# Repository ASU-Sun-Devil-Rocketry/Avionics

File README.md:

<h1>Sun Devil Rocketry Avionics</h1>

This is a repository for all SDR Avionics software and PCB files. Current Projects include:
<ul>
   <li>General Purpose Flight Computer</li>
   <li>Ground Station Launch System</li>
   <li>Strand Burner Ignition and Data Acquisition System</li>
   <li>Liquid Propulsion Propellant Management Controller and Data Acquisition Systems</li>
</ul>
     
Files related to the flight computer and ground station can be found in the general directory. Strand Burner files can be found in the solids directory, and liquid propulsion files can be found in the liquids folder.

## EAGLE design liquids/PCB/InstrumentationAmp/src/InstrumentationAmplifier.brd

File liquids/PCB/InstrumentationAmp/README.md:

<h1>Instrumentation Amplifier with Regulated Dual Supply</h1>

The instrumentation amplifier uses an adjustable gain differential amplifier with buffered inputs to amplify the readings from an analog sensor using a wheatstone bridge such as a load cell or pressure transducer. The operational amplifiers use a dual power supply which is regulated using variable linear voltage regulators.

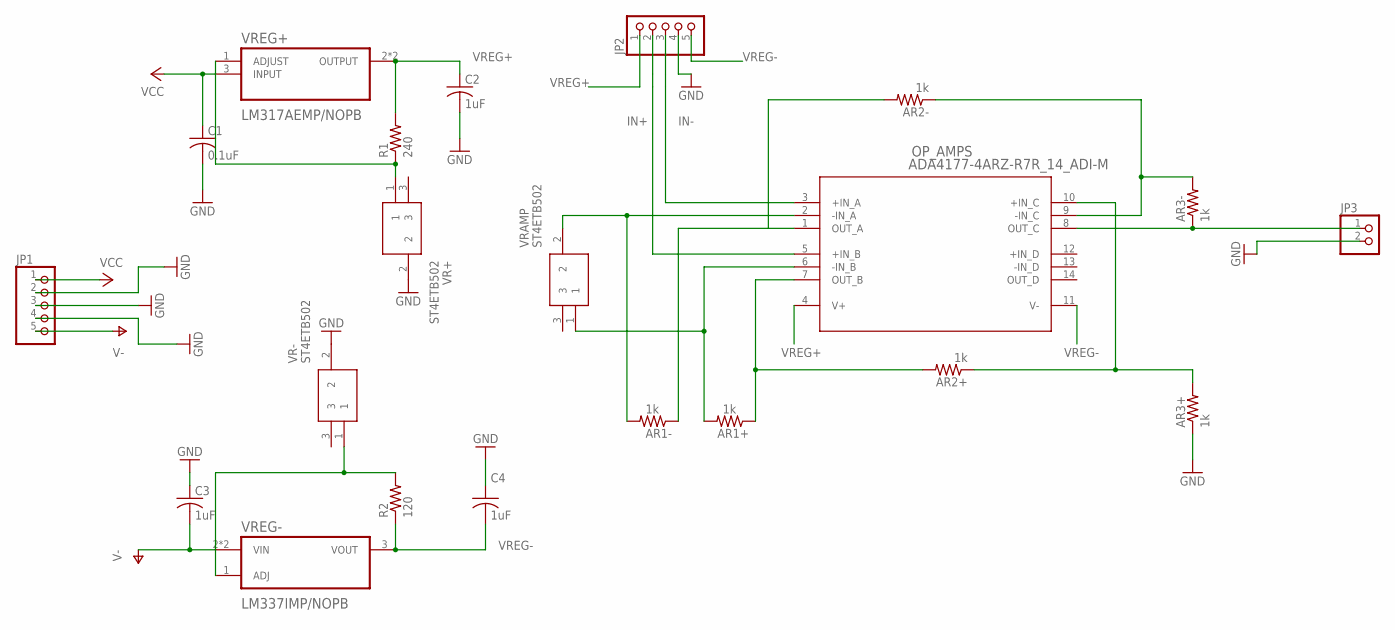
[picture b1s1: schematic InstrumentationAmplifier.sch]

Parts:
AR1+, AR1-, AR2+, AR2-, AR3+, AR3-: 1k; R0603
C1: 0.1uF; C0603
C2, C3, C4: 1uF; C0603
JP1, JP2: PINHD-1X55X2MM; 1_05X2MM
JP3: PINHD-1X2; 1X02
OP_AMPS: ADA4177-4ARZ-R7R_14_ADI-M; R_14_ADI-M
R1: 240; R0603
R2: 120; R0603
VR+: ST4ETB502; ST-4EB
VR-: ST4ETB502; ST-4EB
VRAMP: ST4ETB502; ST-4EB
VREG+: LM317AEMP/NOPB; SOT230P700X180-4N
VREG-: LM337IMP/NOPB; SOT230P700X180-4N

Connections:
GND: AR3+.1, C1.2, C2.2, C3.1, C4.1, JP1.2, JP1.3, JP1.4, JP2.4, JP3.2, VR+.2, VR-.2
IN+: JP2.2, OP_AMPS.5 (+IN_B)
IN-: JP2.3, OP_AMPS.3 (+IN_A)
unnamed: AR2+.1, AR3+.2, OP_AMPS.10 (+IN_C)
unnamed: R1.1, VR+.1, VREG+.1 (ADJUST)
unnamed: AR2-.1, AR3-.2, OP_AMPS.9 (-IN_C)
unnamed: R2.2, VR-.1, VREG-.1 (ADJ)
unnamed: AR1-.1, AR2-.2, OP_AMPS.1 (OUT_A)
unnamed: AR1-.2, OP_AMPS.2 (-IN_A), VRAMP.2
unnamed: AR1+.1, AR2+.2, OP_AMPS.7 (OUT_B)
unnamed: AR1+.2, OP_AMPS.6 (-IN_B), VRAMP.1
unnamed: AR3-.1, JP3.1, OP_AMPS.8 (OUT_C)
V-: C3.2, JP1.5, VREG-.2 (VIN), VREG-.4 (VIN)
VCC: C1.1, JP1.1, VREG+.3 (INPUT)
VREG+: C2.1, JP2.1, OP_AMPS.4 (V+), R1.2, VREG+.2 (OUTPUT), VREG+.4 (OUTPUT)
VREG-: C4.2, JP2.5, OP_AMPS.11 (V-), R2.1, VREG-.3 (VOUT)

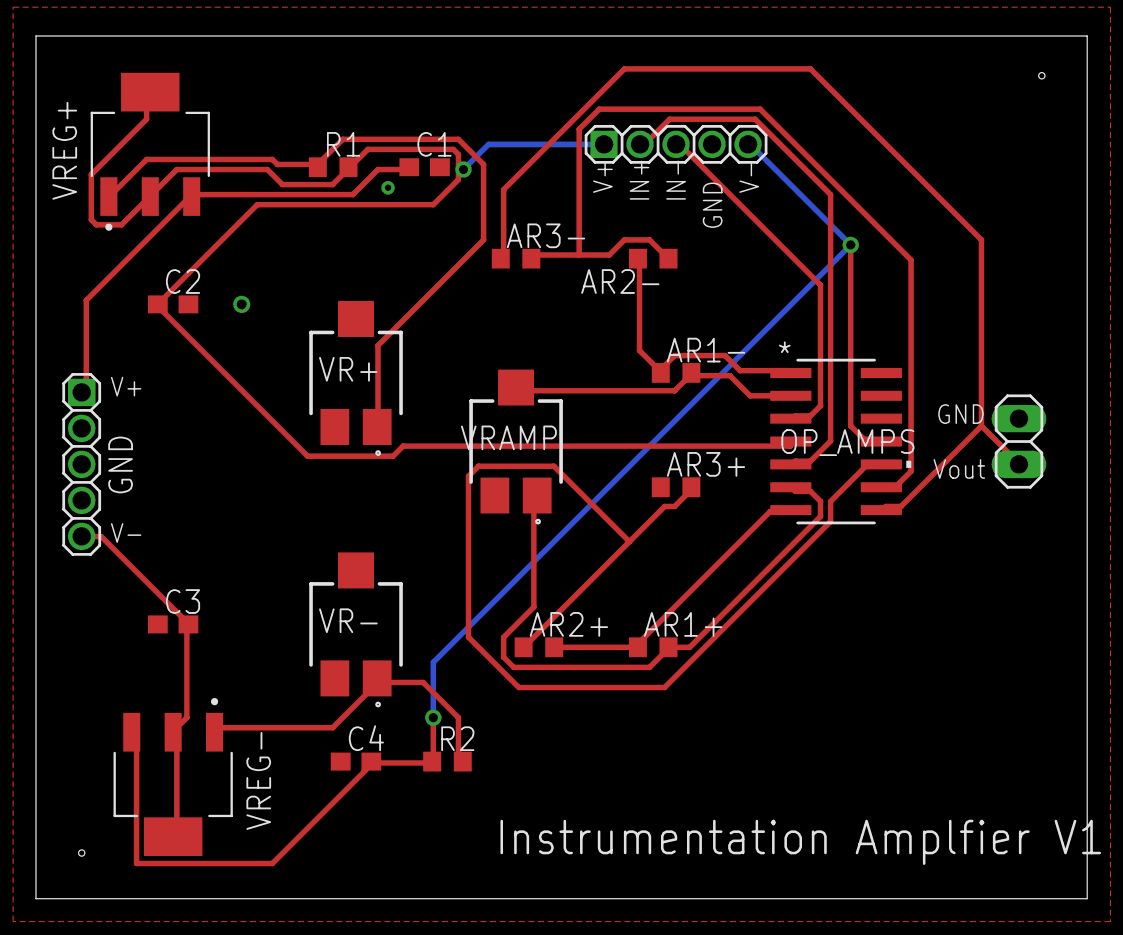
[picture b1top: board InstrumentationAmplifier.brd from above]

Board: 2 copper layers, 58.4 x 47.9 mm, 21 parts (0 on the bottom side), 16 nets.

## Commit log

2021-02-06 Test Push
2021-02-06 removed test folder
2021-02-06 Copied Files from old github
2021-03-20 Changed name of folder from controls to general
2021-03-20 Uploaded PCB files for Instrumentation Amplifier
2021-03-20 Created structure for PCB project directories
2021-03-20 Added pin headers for regualted output
2021-03-20 Added Readme for Liquids PCB directory
2021-03-20 Added README to Avionics General PCB directory
2021-03-20 Rewrote README for general directory
2021-03-20 Testing if README uses html formatting
2021-03-20 Changed README first line to html header
2021-03-20 Added img folder to all PCB directories
2021-03-20 Added image of Instrumentation Amp schematic
2021-03-20 Added datasheets for op-amps and pots
2021-03-26 Added bullet points to README in main directory
2021-03-26 Updated README in root directory
    Completed list of all current avionics projects
2021-03-26 Update README.md
    Fixed backslash issue with unordered list items
2021-03-26 Added reference files for ATMega328 programming in C
2021-03-26 Added placeholder folder for arduino code
2021-03-26 Added README to atmega328 directory
2021-03-26 Changed atmega328p to atmega328
2021-03-26 Added ref note to atmega328 README
2021-03-26 Added datasheet for atmega328
2021-03-26 Test
2021-03-27 Fixed Grammar issue in README
2021-03-31 Wrote Arduino Code for strand burner timing
2021-04-02 Added h1 tags to README
2021-04-02 Added Underline to README title
2021-04-02 Made Bold title
2021-04-02 Indented main lines of README
2021-04-02 Added Board files for instrumentation amplifier
2021-04-03 Finalized Board Files
